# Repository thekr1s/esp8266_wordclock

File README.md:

# Get started on ubuntu 18.04 upto 20.04 (64 bits)
```
git clone https://github.com/thekr1s/esp8266_wordclock.git
cd esp8266_wordclock/esp-open-rtos
# NOTE Bearssl is outdated, and doesn't support CAfile, therefor disable check
git config --global http.sslverify false
git submodule update --init --recursive
cd ..
tar -xvf esp-open-sdk.tgz 
sudo apt-get install make gcc g++
sudo pip install esptool
. env.sh
cd wordclock
make
```

# Program ESP
## Windows
- Install ESP8266Flasher : https://github.com/nodemcu/nodemcu-flasher
- Install the driver for the USB2Sereial http://www.wch.cn/download/CH341SER_ZIP.html

Start the ESP8266Flasher.exe en vul het onderstaande in:

- esp8266_wordclock\esp-open-rtos\bootloader\firmware_prebuilt\rboot.bin            @ 0x00000
- esp8266_wordclock\esp-open-rtos\bootloader\firmware_prebuilt\blank_config.bin     @ 0x01000
- esp8266_wordclock\wordclock\firmware\ws2812_buffer.bin                            @ 0x02000

## Linux
After building the firmware with 'make' as discribed above, type the folliwing command:
```
make do_flash
```

# Setup Wordclock
- hierbenik: the request is build by: sprintf(buf, "GET %s HTTP/1.1\r\nHost: %s\r\nConnection:keep-alive\r\nAccept: */*\r\n\r\n", request, url);
- hierbenik request: "/get_with_age.php

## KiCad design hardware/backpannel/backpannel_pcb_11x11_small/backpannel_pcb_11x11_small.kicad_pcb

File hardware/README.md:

# Parts
## Electronics:
- NodeMcu Lolin V3 ESP32 [Link](https://www.ebay.com/itm/NodeMCU-V3-ESP8266-ESP-12-E-Lua-CH340-WiFI-WLan-IoT-Lolin-Mini-N3A2-V9T3/312753940110)
- Led strip: WS2812B [Link](https://www.ebay.com/itm/1-5m-WS2812B-RGB-Led-Strip-Light-30-60-144Leds-m-Individual-Addressable-IC-DC5V/401755047203?var=671534865138)
- LDR: 5MM GL5537 [Link](https://www.ebay.com/itm/20pcs-Photoresistor-5MM-GL5537-LDR-Photo-Resistors-Light-Dependent-Resistor/381374819080?epid=1381908731&hash=item58cbb5eb08:g:INIAAOxyYSdTAJq4)
- 100kOhm Resistor [link](https://www.ebay.com/itm/100PCS-1-4W-0-25W-Metal-Film-Resistor-1-Full-Range-of-Values-0-to-10M/252838503547?hash=item3ade59647b:m:m9AAPzkedx9P_upvXOpgF9Q) 
- flat cable
- Power wire
- micro USB
- USB A
## Shop / Bouwmarkt:
- For frames clock:
    - Ikea RIBBA frame 23cm [link](https://www.ikea.com/nl/nl/p/ribba-fotolijst-zwart-40378401/)
    - Ikea RIBBA frame 50cm [link](https://www.ikea.com/nl/nl/p/ribba-fotolijst-zwart-00378436/)
- Multiplex timmerplaat gegrond 3 mm 122x61
- MDF 122x61cm 12/15mm
- Hoekprofiel aluminium 12x12/15x15 mm 2 meter
- Bison 2-componentenlijm kombi metaal 24 ml
- Plaatschroef 3x13 mm cilinderkop
## Special:
- letterplate
    - laser cutting: €50.0/€150.0
- led-divider cnc: (time)

# Electronic Wiring
- ESP(Rx) -> Led Strip (Data)
- ESP(GND) -> Led Strip (GND)
- ESP(VU) -> Led Strip (5v)
- LDR(1) -> ESP(GND)
- LDR(2) -> ESP(A0)
- ESP(A0) -> RESISTOR(100kOhm) -> ESP(3v)

- 

# Build Types
The wordclock can be created in 2 sizes because of the used led strip. Its 60 LED's per meter or 30 LED's per meter.
## Normal (Desk size)
- 60 Leds per meter
    - 11x11 letters => 121 LED's => (2.01m) => 3 meter ledstrip
- 12mm MDF plate 23*23 cm
- Hardboard 23*23 cm
### Frame (ikea RIBBA) 

### Frameless

## Big clock (wall size)
The Big clock can be created with 11x11 letters or 13x13 letters
- 30 Leds per meter
    - 11x11 letters => 121 LED's => (4.04m) => 5 meter ledstrip
    - 13x13 letters => 169 LED's => (5.7m) => 6 meter ledstrip
- MDF plate 50*50 cm
- Hardboard 50*50 cm

### Frame 11x11 letters

### Frame 13x13 letters

### Frameless 13x13 letters

# Assemble
The assembly can be divided into the following parts:
- led-panel
- light-divider
- letterplate
- Electronics
## light-divider
### CNC light-divider

### light-divider by hand
For the famed Clock the MDF plate need's to be 23x23 or 50x50 cm. For the frameless the MDF plate can be LxB 21x20 or 45,5x47 but start with 23x23 or 50x50.
The Normal clock can be made with 9mm or 12mm MDF plate.
The big clock can be made with 12mm or 15mm MDF plate.
- Determine the center of the plate by drawing 2 lines
- From the center draw a grid of lines
    - For the 60 led's per meter -> distance between lines is 1.6666 cm
    - For the 30 led's per meter -> distance between lines is 3.3333 cm
- 
- Drill a hole through each line crossing
    - Use a speed drill or a countersink bit
    - For the normal clock the hole is 12mm
    - For the big clock the hole is 30mm
- For the frameless clock the bottom, right and left side can be shorted so the letterplate will floating from the wall ~15mm(aluminium strip width) + 2mm spare
    - The top side is used to hang the clock
- The result should look like the cnc light-divider

## led-panel
- Place the led-panel under the light-divider.
- Trace the first, middle and last holes from the light-divider on the led panel
- Trace the outer line from the light-divider
    - in case of the frameless the top can be shorten 2 cm
- Cut peace’s from the ledstrip, (cut on the line that is drawn on the 3 copper paths)
    - For the 11x11 clock the ledstrip should be 11 leds long 
    - For the 13x13 clock the ledstrip should be 13 leds long 
- Place the led-strips with the led centred on the traces on the hardboard by following the this pattern:
    - Start upper left with Din and place it to the upper Right side end with Dout
    - The second row start with Dout on the left side and ends with Din
    - continue this zigzag pattern until all rows are done
- Use a Flat cable to connect the ledstrips from Dout to Din.
    - Cut flat cable, strip and tin both ends, cut the both ends so they are separated from each other
    - pre-solder both ends of the ledstrip
    - Start upper right with Dout solder all 3 pins(GND, Dout, 5V) Fold the flat cable 90 degrees down, fold it 90 degrees towards Din Solder again
- drill a hole next to the first led, and next to the last led
- Connect power supply from the first led to the last led with the red/black wire
- Connect the powers supply and the Din with the ESP (see Electronic Wiring)
- 
- You should be able to test the LED panel by connection the ESP to its power supply

## Connect the led-panel with the light-divider
- Place the light-divider on the led-panel and make sure all leds are centred
- Drill (1.5mm) hole through both panels. These hols can later be used to connect both panels
- Flip it and screw both panels to each other.
- Frameless ESP placement
    - Big clock place the ESP in the upper right corner (hot glue)
    - Normal clock the ESP will be screwed to the back
- 

## Diffuser (to be improved)
- place the paper over the light-divider and cut it on size
- make sure its stays in place with tape

## Letterplate
### frame
- Connect the LDR and the resistor (see Electronic Wiring)
- fix the ESP with a screw to the back of the led-panel
- Place the letterplate and the light divider in the frame
- place some foam in the back so all is pushed forwarded
- Close the frame
### frameless
- Center the light-divider on the letterplate and drill the LDR hole
- Draw the outer line from the light-divider on theletterplates back
- Cut the aluminium strip so it fits nicely around the light-divider (left, right and bottom)
- Make both the letterplate and the aluminium strip rough with sanding paper
- drill 3 holes in all aluminium strips (used for connecting the letterplate to the light-divider)
- glue the aluminium strip on the letterplate (use glue clamps) wait 24 hours
- screw the letterplate to the light-divider
- 

# Hardware Drawings
## letterplate
- I Have created a FreeCAD pyhton macro for generating a Letterplate, ..\hardware\lettering_plates\FreeCAD_drawings\freecad_macro
- The letterplate is parametric so can be used for 11*11 of 13*13
- After the generation is done, export the part as .STEP (the DXF generator from freecad is not smooth)
- FreeCAD export DXF WORKS (0.18.4):
    - Edit -> Preference -> Inport-Export -> DXF
    - Max Spline Segment to 0,1 or 0,01 mm (NOTE use , instead of .)
    - Select all elements
    - File -> Export -> Autodesk DXF 2d
- Import the .STEP file into Fusion for creating the DXF file of gcode
- G-code
    - Create A body by setting the Hight
    - Switch to manufacture
    - start creating the Gcode
- DXF:
    - Create a sketch on the Top view
    - Menu -> Create -> Project / include -> include 3D Geometry
    - Select the Body from the letterplate
    - Save Sketch -> right klik the Sketch and save as DXF
## ledschotten
- The LDR for the 11*11 clock is 214.444 mm from the bottom (This information is printed by FreeCAD)
- The LDR for the 13*13 clock is 477.778 mm from the bottom
- The LEDschotten is completely drawn in Fusion360, and is partly parametric.

# Tips & tricks:
- The MDF plate can also be replaced by "Foamed pvc"

# Note:
The NodeMcu Lolin V3 is needed because the Lolin has a 3v reference voltage for its adc that is used for the LDR all other NodeMC have 1v reference voltage

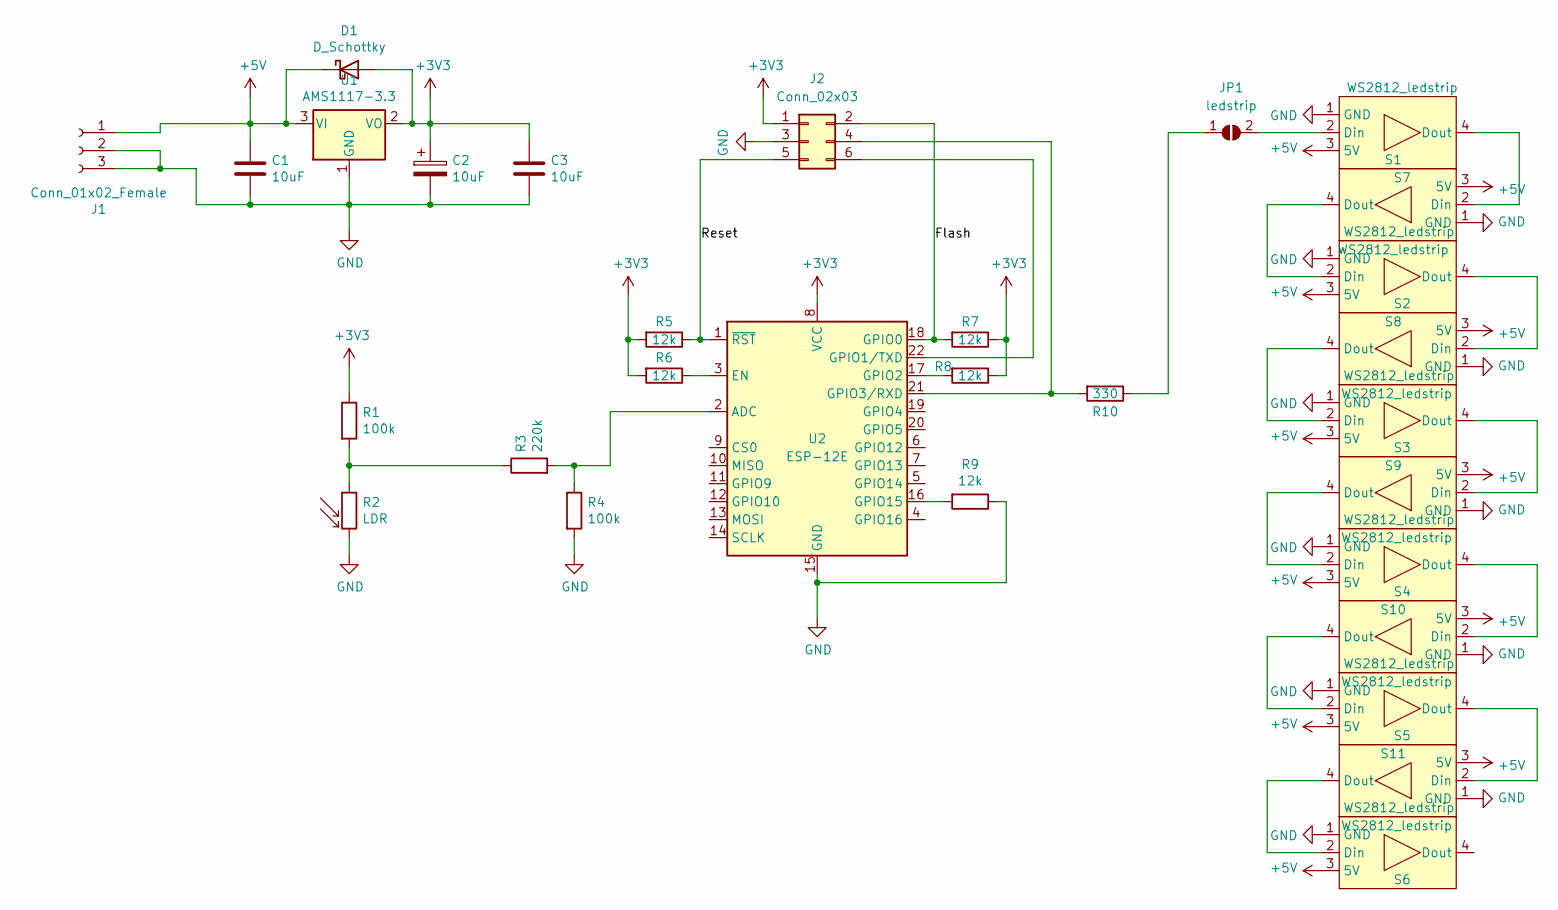
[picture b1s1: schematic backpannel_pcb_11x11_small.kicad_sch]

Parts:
C1, C3: 10uF; C_0805_2012Metric_Pad1.18x1.45mm_HandSolder
C2: 10uF; CP_Elec_6.3x5.4
D1: D_Schottky; D_0805_2012Metric_Pad1.15x1.40mm_HandSolder
J1: Conn_01x02_Female; BarrelJack_CLIFF_FC681465S_SMT_Horizontal
J2: Conn_02x03; PinHeader_2x03_P2.54mm_Vertical
JP1: ledstrip; SolderJumper-2_P1.3mm_Open_RoundedPad1.0x1.5mm
R1, R4: 100k; R_0805_2012Metric_Pad1.20x1.40mm_HandSolder
R2: LDR; R_LDR_5.1x4.3mm_P3.4mm_Vertical
R3: 220k; R_0805_2012Metric_Pad1.20x1.40mm_HandSolder
R5, R6, R7, R8, R9: 12k; R_0805_2012Metric_Pad1.20x1.40mm_HandSolder
R10: 330; R_0805_2012Metric_Pad1.20x1.40mm_HandSolder
S1, S2, S3, S4, S5, S6, S7, S8, S9, S10, S11: WS2812_ledstrip; WS2812_ledstrip_60leds_meter
U1: AMS1117-3.3; SOT-223-3_TabPin2
U2: ESP-12E

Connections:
+3V3: C2.1, C3.1, D1.2 (A), J2.1, R1.1, R5.2, R6.2, R7.1, R8.1, U1.2 (VO), U2.8 (VCC)
+5V: C1.1, D1.1 (K), J1.1, S1.3 (5V), S2.3 (5V), S3.3 (5V), S4.3 (5V), S5.3 (5V), S6.3 (5V), S7.3 (5V), S8.3 (5V), S9.3 (5V), S10.3 (5V), S11.3 (5V), U1.3 (VI)
/Flash: J2.2, R7.2, U2.18 (GPIO0)
/Reset: J2.5, R5.1, U2.1 (~RST)
GND: C1.2, C2.2, C3.2, J1.2, J1.3, J2.3, R2.2, R4.2, R9.1, S1.1 (GND), S2.1 (GND), S3.1 (GND), S4.1 (GND), S5.1 (GND), S6.1 (GND), S7.1 (GND), S8.1 (GND), S9.1 (GND), S10.1 (GND), S11.1 (GND), U1.1 (GND), U2.15 (GND)
unnamed: J2.4, R10.2, U2.21 (GPIO3/RXD)
unnamed: J2.6, U2.22 (GPIO1/TXD)
unnamed: JP1.1 (A), R10.1
unnamed: JP1.2 (B), S1.2 (Din)
unnamed: R1.2, R2.1, R3.1
unnamed: R3.2, R4.1, U2.2 (ADC)
unnamed: R6.1, U2.3 (EN)
unnamed: R8.2, U2.17 (GPIO2)
unnamed: R9.2, U2.16 (GPIO15)
unnamed: S1.4 (Dout), S7.2 (Din)
unnamed: S2.2 (Din), S7.4 (Dout)
unnamed: S2.4 (Dout), S8.2 (Din)
unnamed: S3.2 (Din), S8.4 (Dout)
unnamed: S3.4 (Dout), S9.2 (Din)
unnamed: S4.2 (Din), S9.4 (Dout)
unnamed: S4.4 (Dout), S10.2 (Din)
unnamed: S5.2 (Din), S10.4 (Dout)
unnamed: S5.4 (Dout), S11.2 (Din)
unnamed: S6.2 (Din), S11.4 (Dout)

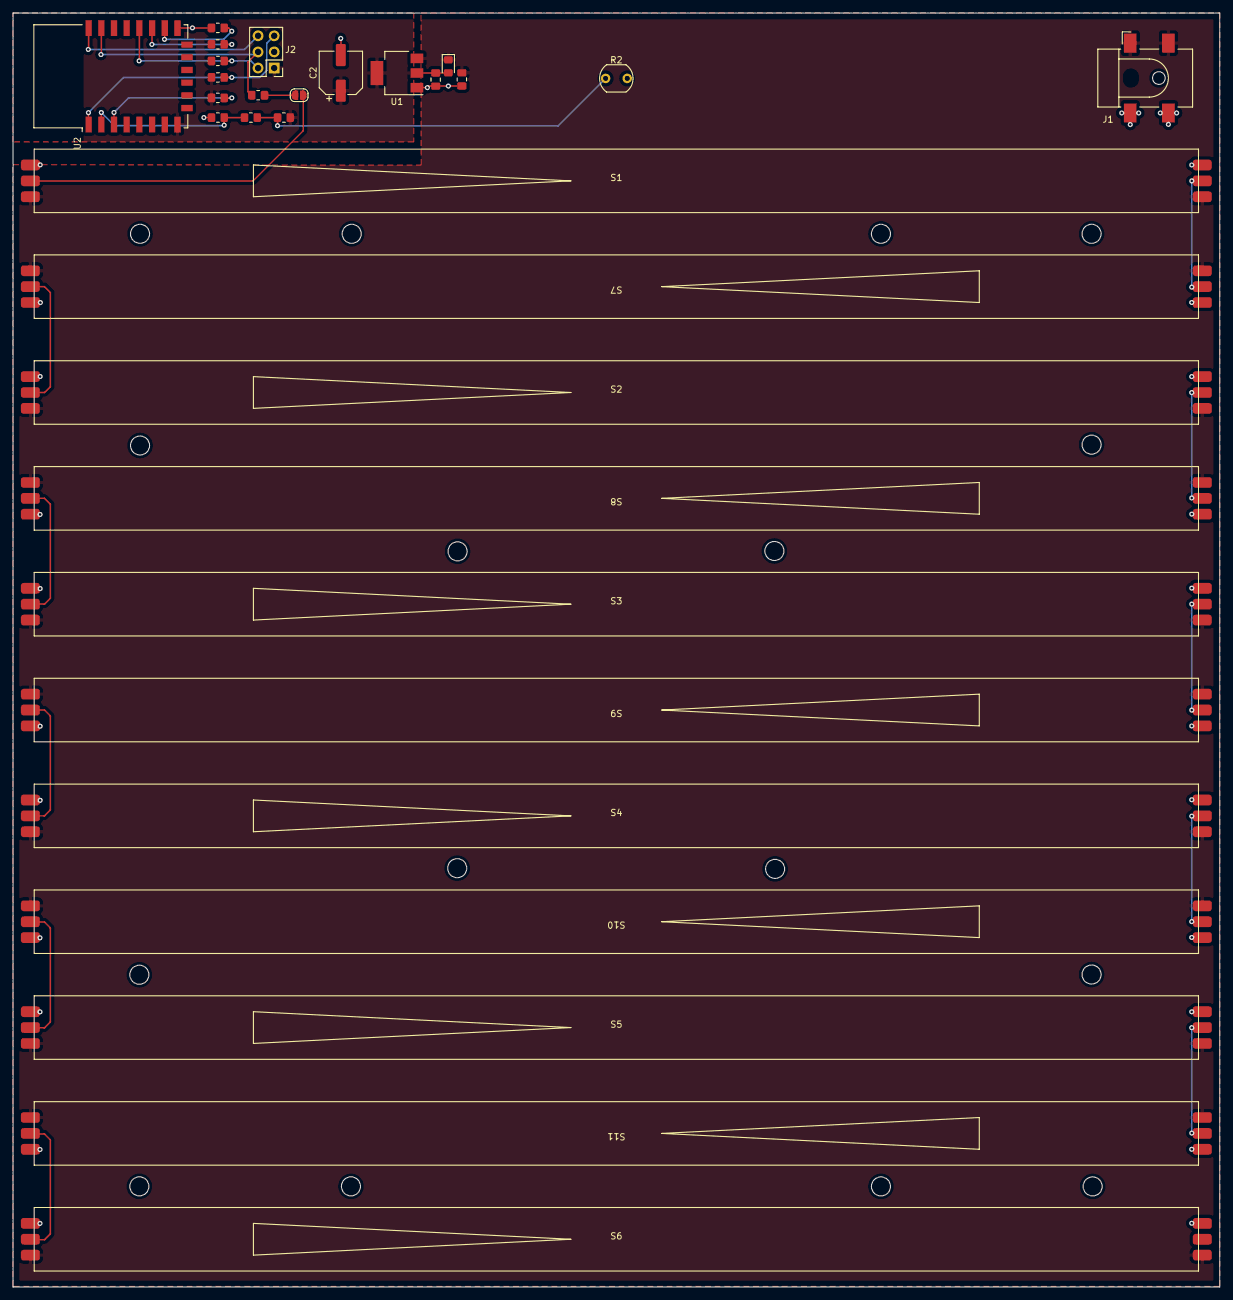
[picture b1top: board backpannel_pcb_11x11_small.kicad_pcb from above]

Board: 2 copper layers, 190.0 x 200.6 mm, 30 parts (0 on the bottom side), 24 nets.

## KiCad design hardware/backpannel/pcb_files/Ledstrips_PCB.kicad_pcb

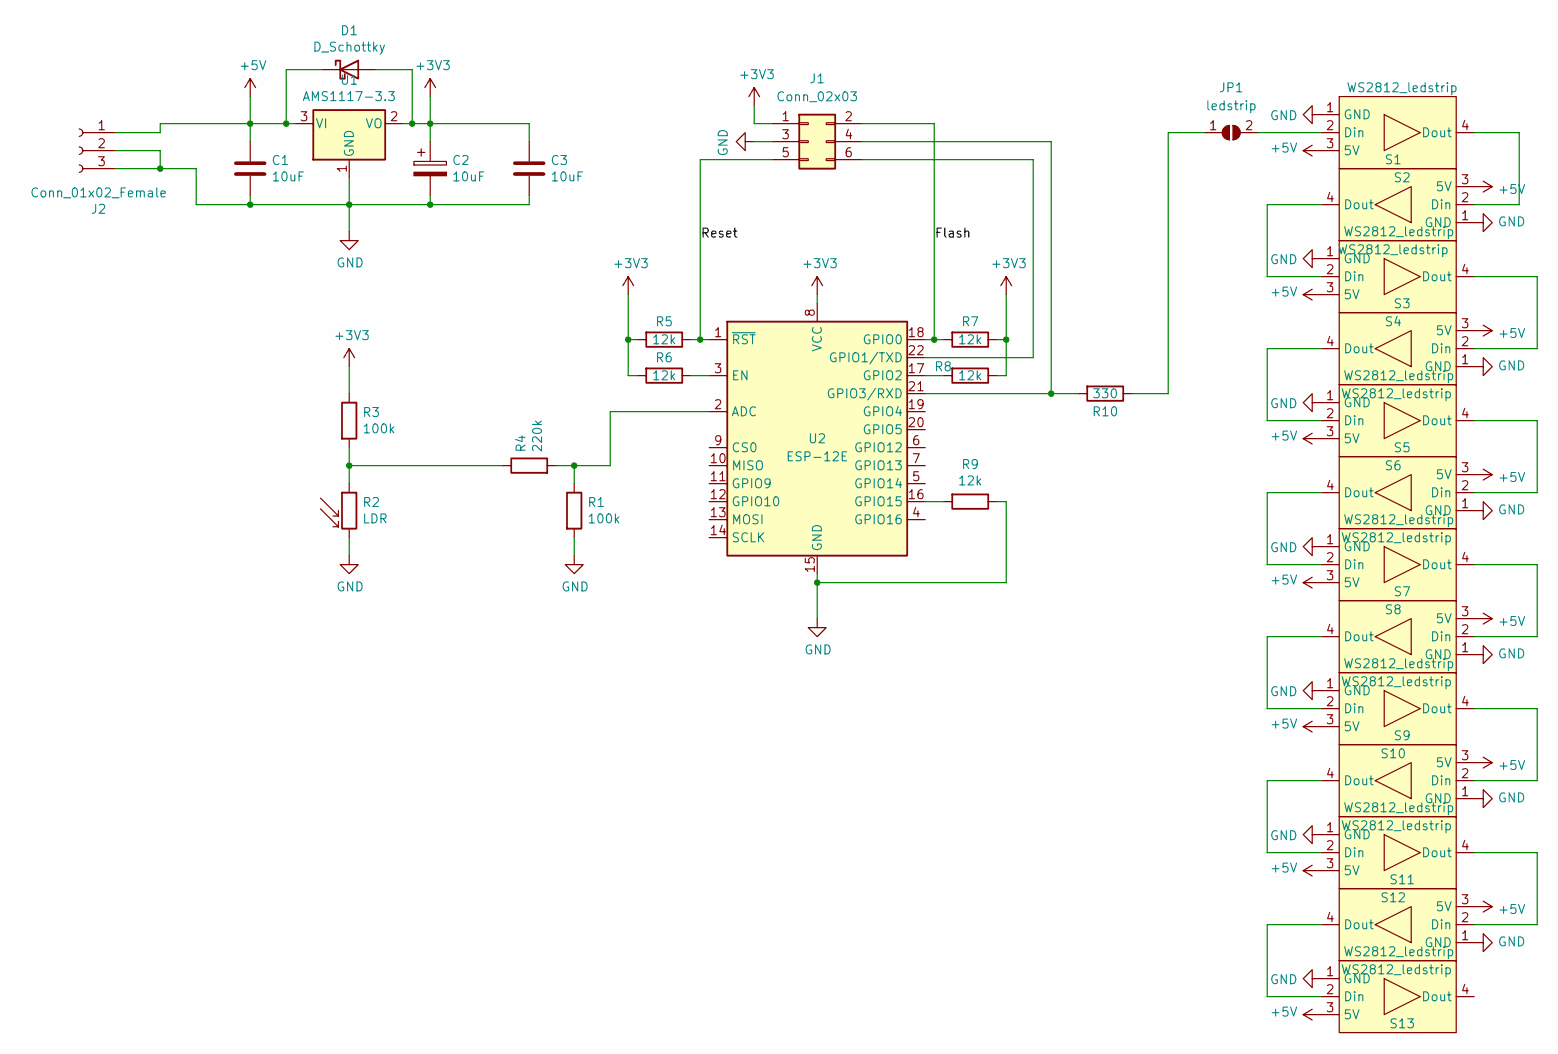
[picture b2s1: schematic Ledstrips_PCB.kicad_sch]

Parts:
C1, C3: 10uF; C_0805_2012Metric_Pad1.18x1.45mm_HandSolder
C2: 10uF; CP_Elec_6.3x5.4
D1: D_Schottky; D_0805_2012Metric_Pad1.15x1.40mm_HandSolder
J1: Conn_02x03; PinHeader_2x03_P2.54mm_Vertical
J2: Conn_01x02_Female; BarrelJack_CLIFF_FC681465S_SMT_Horizontal
JP1: ledstrip; SolderJumper-2_P1.3mm_Open_RoundedPad1.0x1.5mm
R1, R3: 100k; R_0805_2012Metric_Pad1.20x1.40mm_HandSolder
R2: LDR; R_LDR_5.1x4.3mm_P3.4mm_Vertical
R4: 220k; R_0805_2012Metric_Pad1.20x1.40mm_HandSolder
R5, R6, R7, R8, R9: 12k; R_0805_2012Metric_Pad1.20x1.40mm_HandSolder
R10: 330; R_0805_2012Metric_Pad1.20x1.40mm_HandSolder
S1, S2, S3, S4, S5, S6, S7, S8, S9, S10, S11, S12, S13: WS2812_ledstrip; WS2812_ledstrip_30leds_meter
U1: AMS1117-3.3; SOT-223-3_TabPin2
U2: ESP-12E

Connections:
+3V3: C2.1, C3.1, D1.2 (A), J1.1, R3.1, R5.2, R6.2, R7.1, R8.1, U1.2 (VO), U2.8 (VCC)
+5V: C1.1, D1.1 (K), J2.1, S1.3 (5V), S2.3 (5V), S3.3 (5V), S4.3 (5V), S5.3 (5V), S6.3 (5V), S7.3 (5V), S8.3 (5V), S9.3 (5V), S10.3 (5V), S11.3 (5V), S12.3 (5V), S13.3 (5V), U1.3 (VI)
/Flash: J1.2, R7.2, U2.18 (GPIO0)
/Reset: J1.5, R5.1, U2.1 (~RST)
GND: C1.2, C2.2, C3.2, J1.3, J2.2, J2.3, R1.2, R2.2, R9.1, S1.1 (GND), S2.1 (GND), S3.1 (GND), S4.1 (GND), S5.1 (GND), S6.1 (GND), S7.1 (GND), S8.1 (GND), S9.1 (GND), S10.1 (GND), S11.1 (GND), S12.1 (GND), S13.1 (GND), U1.1 (GND), U2.15 (GND)
unnamed: J1.4, R10.2, U2.21 (GPIO3/RXD)
unnamed: J1.6, U2.22 (GPIO1/TXD)
unnamed: JP1.1 (A), R10.1
unnamed: JP1.2 (B), S1.2 (Din)
unnamed: R1.1, R4.2, U2.2 (ADC)
unnamed: R2.1, R3.2, R4.1
unnamed: R6.1, U2.3 (EN)
unnamed: R8.2, U2.17 (GPIO2)
unnamed: R9.2, U2.16 (GPIO15)
unnamed: S1.4 (Dout), S2.2 (Din)
unnamed: S2.4 (Dout), S3.2 (Din)
unnamed: S3.4 (Dout), S4.2 (Din)
unnamed: S4.4 (Dout), S5.2 (Din)
unnamed: S5.4 (Dout), S6.2 (Din)
unnamed: S6.4 (Dout), S7.2 (Din)
unnamed: S7.4 (Dout), S8.2 (Din)
unnamed: S8.4 (Dout), S9.2 (Din)
unnamed: S9.4 (Dout), S10.2 (Din)
unnamed: S10.4 (Dout), S11.2 (Din)
unnamed: S11.4 (Dout), S12.2 (Din)
unnamed: S12.4 (Dout), S13.2 (Din)

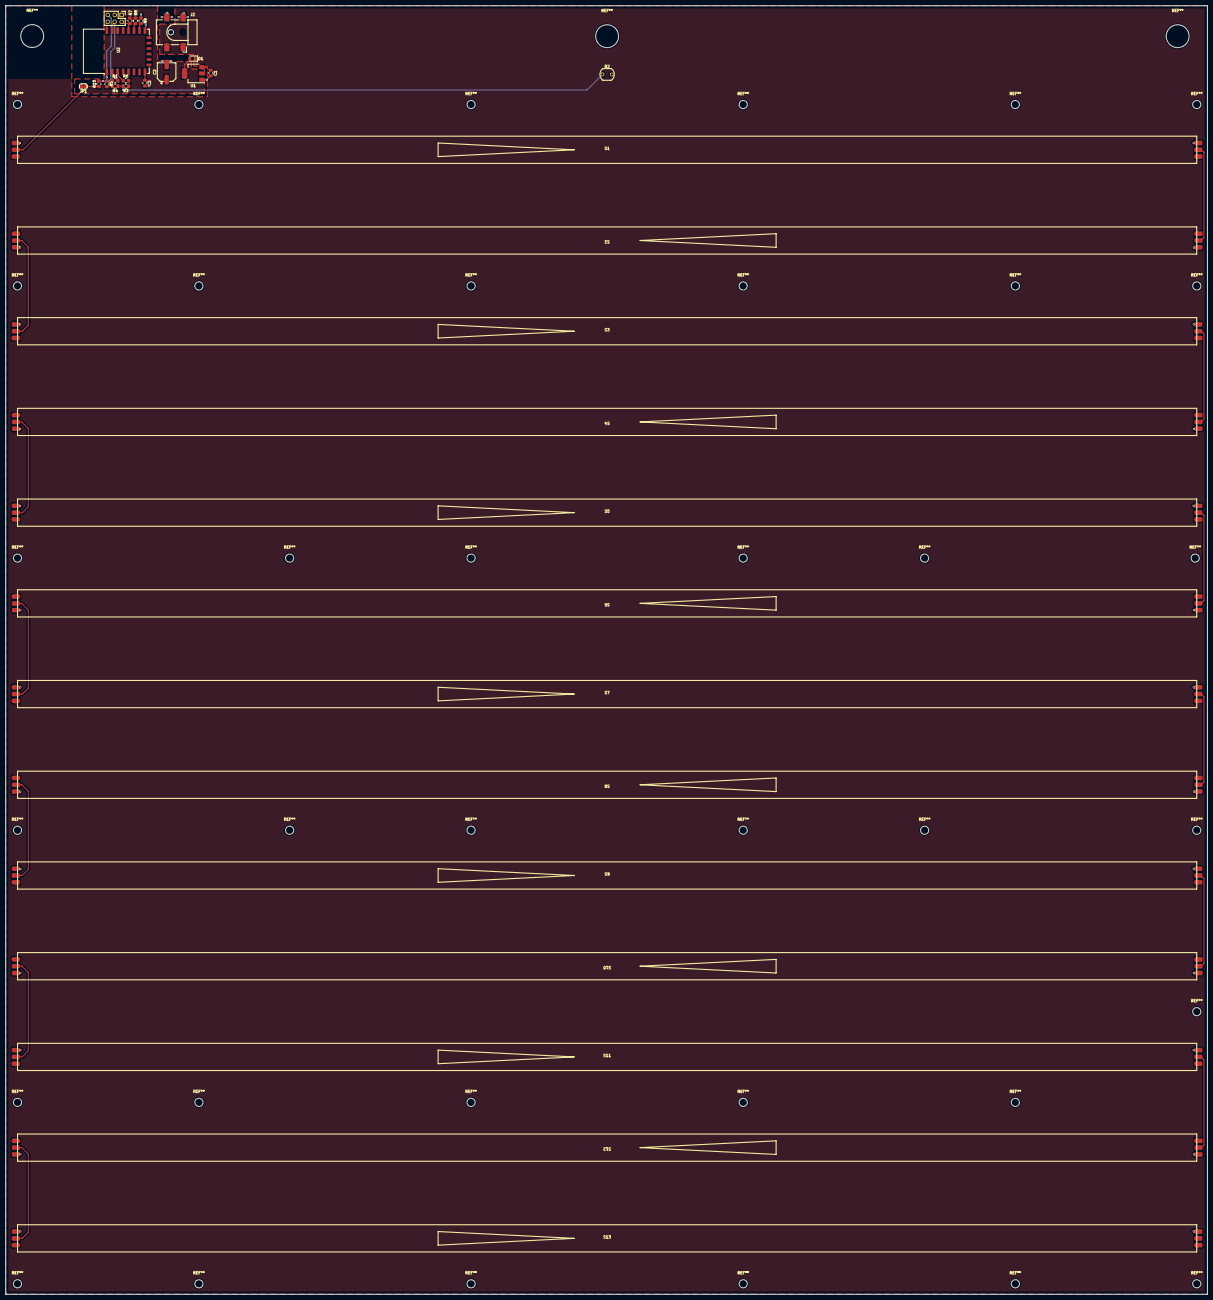
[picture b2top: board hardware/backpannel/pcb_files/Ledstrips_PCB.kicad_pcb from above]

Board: 2 copper layers, 441.6 x 473.5 mm, 32 parts (0 on the bottom side), 26 nets.

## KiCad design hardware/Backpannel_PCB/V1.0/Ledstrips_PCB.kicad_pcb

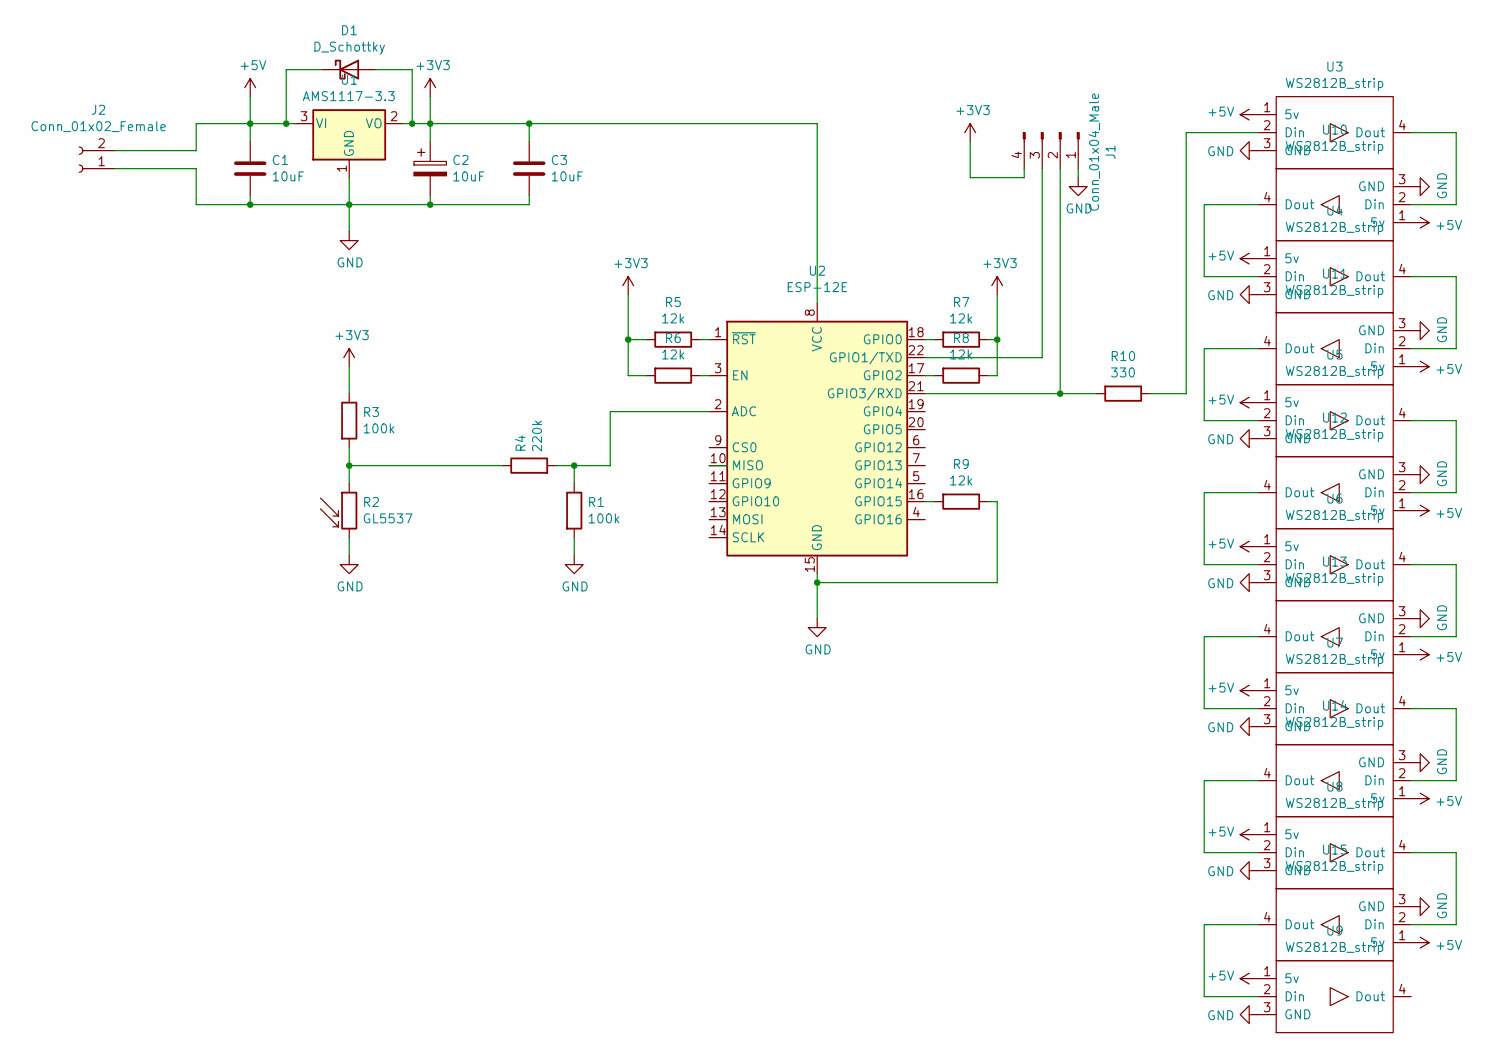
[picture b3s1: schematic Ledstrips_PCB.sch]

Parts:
C1, C3: 10uF; C_0603_1608Metric_Pad1.08x0.95mm_HandSolder
C2: 10uF; CP_Elec_3x5.4
D1: D_Schottky; D_0603_1608Metric_Pad1.05x0.95mm_HandSolder
J1: Conn_01x04_Male; PinHeader_1x04_P2.54mm_Vertical
J2: Conn_01x02_Female; BarrelJack_CLIFF_FC681465S_SMT_Horizontal
R1, R3: 100k; R_0603_1608Metric_Pad0.98x0.95mm_HandSolder
R2: GL5537; R_LDR_5.0x4.1mm_P3mm_Vertical
R4: 220k; R_0603_1608Metric_Pad0.98x0.95mm_HandSolder
R5, R6, R7, R8, R9: 12k; R_0603_1608Metric_Pad0.98x0.95mm_HandSolder
R10: 330; R_0603_1608Metric_Pad0.98x0.95mm_HandSolder
U1: AMS1117-3.3; SOT-223-3_TabPin2
U2: ESP-12E
U3, U4, U5, U6, U7, U8, U9, U10, U11, U12, U13, U14, U15: WS2812B_strip; ws2812_ledstrip

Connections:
+3V3: C2.1, C3.1, D1.2 (A), J1.4, R3.1, R5.2, R6.2, R7.1, R8.1, U1.2 (VO), U2.8 (VCC)
+5V: C1.1, D1.1 (K), J2.2, U1.3 (VI), U3.1 (5v), U4.1 (5v), U5.1 (5v), U6.1 (5v), U7.1 (5v), U8.1 (5v), U9.1 (5v), U10.1 (5v), U11.1 (5v), U12.1 (5v), U13.1 (5v), U14.1 (5v), U15.1 (5v)
GND: C1.2, C2.2, C3.2, J1.1, J2.1, R1.2, R2.2, R9.1, U1.1 (GND), U2.15 (GND), U3.3 (GND), U4.3 (GND), U5.3 (GND), U6.3 (GND), U7.3 (GND), U8.3 (GND), U9.3 (GND), U10.3 (GND), U11.3 (GND), U12.3 (GND), U13.3 (GND), U14.3 (GND), U15.3 (GND)
unnamed: J1.2, R10.2, U2.21 (GPIO3/RXD)
unnamed: J1.3, U2.22 (GPIO1/TXD)
unnamed: R1.1, R4.2, U2.2 (ADC)
unnamed: R2.1, R3.2, R4.1
unnamed: R5.1, U2.1 (~RST)
unnamed: R6.1, U2.3 (EN)
unnamed: R7.2, U2.18 (GPIO0)
unnamed: R8.2, U2.17 (GPIO2)
unnamed: R9.2, U2.16 (GPIO15)
unnamed: R10.1, U3.2 (Din)
unnamed: U3.4 (Dout), U10.2 (Din)
unnamed: U4.2 (Din), U10.4 (Dout)
unnamed: U4.4 (Dout), U11.2 (Din)
unnamed: U5.2 (Din), U11.4 (Dout)
unnamed: U5.4 (Dout), U12.2 (Din)
unnamed: U6.2 (Din), U12.4 (Dout)
unnamed: U6.4 (Dout), U13.2 (Din)
unnamed: U7.2 (Din), U13.4 (Dout)
unnamed: U7.4 (Dout), U14.2 (Din)
unnamed: U8.2 (Din), U14.4 (Dout)
unnamed: U8.4 (Dout), U15.2 (Din)
unnamed: U9.2 (Din), U15.4 (Dout)

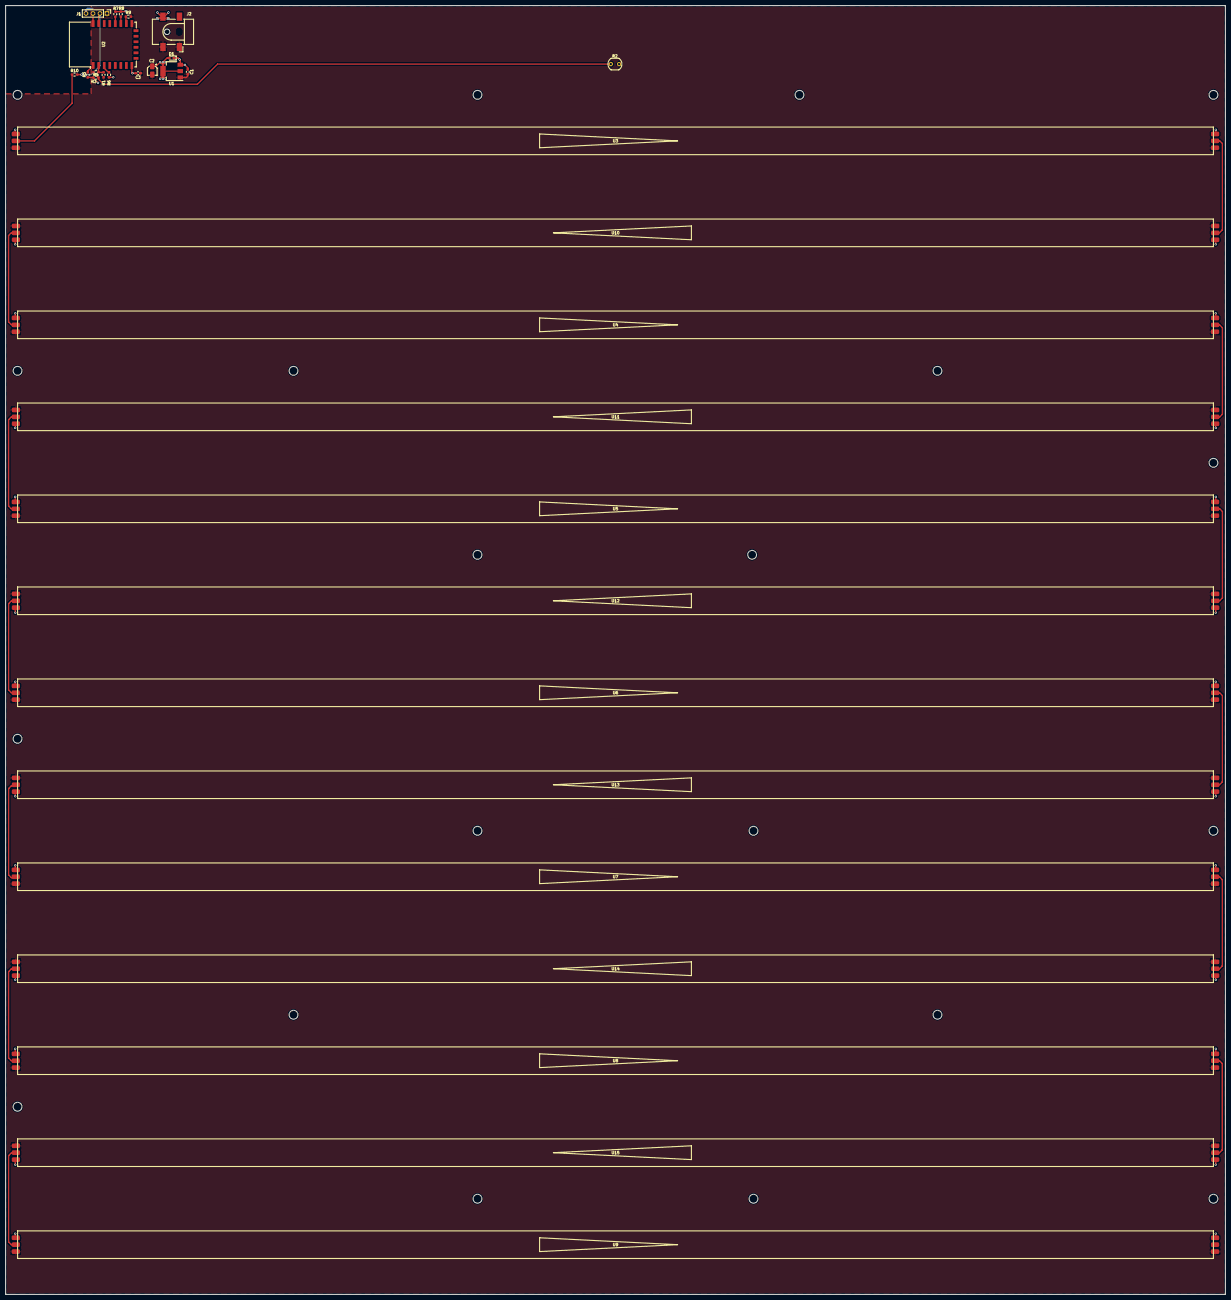
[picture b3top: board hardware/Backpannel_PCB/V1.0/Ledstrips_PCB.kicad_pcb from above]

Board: 2 copper layers, 442.0 x 467.0 mm, 31 parts (0 on the bottom side), 25 nets.

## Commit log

2018-02-27 Initial comit from svn archive
2018-02-28 add esp-open-rtos patch
2018-02-28 ad toolchain in tar update readme
2018-02-28 remove svnversion from makefile
2018-03-02 Add wipe effect
2018-03-02 add the color rainbow
2018-03-02 fixed 13*13 word faults
2018-03-03 Hierbenik implemented for rutger
2018-03-03 small change to the readme
2018-03-03 added a git ignore file for build results
2018-03-11 increase wipe refresh speed
2018-03-15 renamed ALSFILER_RANDOM
2018-04-05 Add hostname to dhcp request
2018-04-05 undo previous commit
2018-10-22 add git version number in build
2018-10-23 display message when no wifi connection
2019-08-17 includes all my spilt files into this git repo so i/we don't loose any information, it still need some cleaning
2019-08-18 Included freecad tekening
2019-08-18 saved a wordclock without squares
2019-08-20 Freecad draw schotten
2019-08-23 impl for big scots
2019-09-05 split the code into modules, and made a 11X11 clock
2019-09-09 created own font, and some fixes for 11*11 clock
2019-09-09 moved freecad folder
2019-09-25 removed wrong DXF files and fix import
2019-09-25 moved files
2019-11-18 Fix good rainbow color ;-)
2019-11-18 fix rainbow
2019-11-20 update hardware
2019-11-25 uploaded letterplate 11x11 and made env.sh system independed
2019-11-26 letterplaten en gatenboards
2019-11-26 verplaats gatenboard
2019-11-26 add came controller and breakout first version
2019-12-30 updated hardware drawings
2019-12-30 Made Personalized setting configurable through hwcfg
2019-12-30 fix empty settings, and checkbox default on
2019-12-30 also do not clear port number and "wacht even" under perfect imperfections
2019-12-30 Show the current settings in the webpage
2020-01-01 fix checkbox unselected
2020-01-04 fix code revieuw RWA
2020-01-05 default ota server and fix zerotermination
2020-01-05 Removed esp-open-rtos
2020-01-05 Added new version of esp-open-rtos as submodule
2020-01-05 made the new esp_open_rtos build (still a bug in the ledstrip driver)
2020-01-06 change from 3 to 4 bits per pixel
2020-01-07 fixed private_ssid_config
2020-01-22 tetris wip. Not done yet
2020-01-24 apply rainbow filter before hierbenik position to make it more visible
2020-01-24 configurable home location
2020-01-25 fix bool build problem
2020-01-25 remove commented code
2020-01-27 Fix stack crash when in AP mode
2020-01-27 get rid of rtos patches
2020-01-27 fix compiler warnings
2020-01-28 hopefully fix klok op hol
2020-01-29 web pages update
2020-02-02 WIFI AP config via dropdown select
2020-02-02 increase flash upload speed
2020-02-02 reduce debug print outout
2020-02-12 process review
2020-02-12 freecad macro changes
2020-02-15 Upload last generated version of letterplaats G-code
2020-02-22 Revert "Update freecad macro"
2020-02-22 Updated the 11x11 and 13x13 letterplate for RHU, liberation is smoother now, removed unneded points in font to create nice arc
2020-03-06 add kiremko logo
2020-03-11 fix breakout
2020-04-07 add the new drawings RHU
2020-04-18 Changed esp-open-rtos url to own fork
2020-04-18 revert sntp_client
2020-04-20 Initial impl for captive DNS
2020-04-20 Fixed assert in OS, and lower the wordclock main so AP mode has more time
2020-04-20 revert prio change will fix in a other branch
2020-04-20 Cleanup hardware drawing RHU
2020-04-20 Initial captive DNS
2020-04-20 Fix hardware readme
2020-04-21 Update Makefile
    Remove high speed flash programming as it is suspected to destroy the flash
2020-04-22 quick fix for settings
2020-04-23 Added fixed hardware drawing
2020-04-23 Settings are stored throug the sysparam key=value
2020-04-23 update esp-open-rtos for new wifi-cfg
2020-04-23 fixed some logging and dontt run the wordklok main when we have no time
2020-04-23 keep default settings in flash, not ram
2020-04-24 added some sleeps in woordklokmain
2020-04-25 reorderd init and fixed some concurrensi issues
2020-04-29 kill the wordclock task when there is no wifi
2020-04-29 changed prio
2020-04-30 fault handling in starting http server
2020-04-30 remove URLs from readme
2020-05-01 Fix issue when sntp is out of sync
2020-05-01 Made the HTTP socket reusable
2020-05-02 add params to esptools in makefile
2020-05-03 add old firmware binary
2020-05-09 rename to woordklok.bin
2020-05-09 Update build.yml
    A
2020-05-10 Initial merge
2020-05-10 decreased sntp stack
2020-05-11 Processed review comment RWA
2020-05-11 Initial impl for sysparam fix
2020-05-12 Final version of sysparam test
2020-05-12 Moved the connection check in a task so the esp framework finishs its init before starting in ap mode
2020-05-14 Increased woordklok display task prio
2020-05-14 revert dns server code
2020-05-15 Added the release binary
2020-07-10 None functional only hardware en readme changes
2020-07-10 Initial version need to be tested (but nog ESP at work)
2020-07-10 fix logging
2020-07-11 fixed HTML layout
2020-07-11 changed setting magic
2020-07-13 Initial impl
2020-07-17 Correct Time on boot properly
2020-08-03 Captive DNS within our own website
2020-08-05 Update http_server.c
    Resolve merge conflict (FW type was missing)
2020-08-05 fix email address on web page
2020-08-06 Add break after, refresh page
2020-08-08 Initial version for color picker and better response for wifi ap scan
2020-08-11 improve wifi minitor task
2020-08-11 initial version http ota update
2020-08-15 Fixed ap scan task
2020-08-28 set http as default
2020-08-30 Revert "Merge pull request #44 from thekr1s/ubuntu_20.04"
    This reverts commit 86ca58a5fa7ca427b36f4038e63310cc08924adf, reversing
    changes made to b96e6bfef97ccbdc93eba87d549ee790450c63f4.
2020-09-01 strip CRC from firmware file
2020-09-01 do not erase wifi settings on factory reset
2020-09-06 Color picker with embedded IRO.js
2020-09-06 add letterplate_13_13
2020-09-06 only strip crc from binary when make do_flash
2020-09-06 some styling, and forced Saturation and Alpha for background color
2020-09-06 remove comment
2020-09-06 Rutgers Build default settings
2020-09-06 More robust color picker
2020-09-06 use esp-open-rtos from fork on thekr1s
2020-09-12 Revert make file to strip CRC default
2020-09-12 Make the rainbow effect working again
2020-09-12 Removed Background color offset
2020-09-12 Removed the color picker popup
2020-09-12 white space
2020-09-12 Fix color picker scaling for android Chrome
2020-09-12 Fix hangup in http server when client is not properly closing socket
2020-10-12 inital change, needs spelling check and reread it
2020-10-24 Spell checker
2020-10-24 Forget file...
2020-11-14 Move version info to system config tab
2020-11-14 fix in reboot clock
2020-11-14 update connect to wifi text
2020-11-14 sort AP list by strength
2020-11-14 shorten no wifi sentence
2020-11-14 set stationmode befere restart
2020-11-18 fix wifi cinfig in httpsvr
2020-11-19 add IJ to taurus font
2020-11-20 drawing 120x120 housing
2020-11-22 120 housing update
2020-12-30 manual update
2021-01-23 Reduce mem usage to preven alloc error at otaupdate
2021-01-24 improve backgroung handling
2021-01-24 put timesync error indication at top right
2021-02-27 bump esp-open-rtos
2021-02-28 fix button handling
2021-05-16 Set random color every hour
2021-05-16 move MAX macro
2021-05-16 spaces
2021-05-16 more spaces
2021-11-24 initial RGB to RGBW support
2021-12-01 fix enum numer
2021-12-18 added debug webpage for LDR and way to use rgbw ledstrip without the white led
2021-12-18 First version of PCB
2021-12-21 Added non accurate time for 13x13
2021-12-21 Remove unwaded make flag
2021-12-28 added new line
2022-02-02 Fixed fire animation for 13x13 clock
2022-02-02 renamed folder
2022-02-02 rename
2022-02-09 Initial change
2022-02-09 Add install instructions
2022-02-16 13x13 letterplate V2
2022-02-16 Added Qcad converted file
2022-02-23 PCB in between commit
2022-02-23 wifi soft AP accourding to sdk status
2022-03-09 Also updated to HTTP server (tftp is block by some modums)
2022-03-20 don't store the white value in the frame buffer
2022-03-22 Moved copy action to write function
2022-03-22 cleanup names in callback
2022-03-22 Added the new letterplate to the SW
2022-04-20 Fix 13x13 layout, and buffer size
2022-05-04 Added extra SNTP servers through sntp.h (see submodule), fixed core lock, refactord wificfg
2022-05-04 Removed the button task and event handler
2022-05-04 Splitted settings into two flash partitions, with separated magics
2022-05-07 Added reserved space in both setting so the magic is more stable
2022-05-08 All set opmode in 1 task, and cleanup statemachine
2022-05-11 Fixed reboot issues
2022-05-11 Cleaner stop of soft AP
2022-05-30 None functional, only pointed to the proper esp-open-rtos branch
2022-06-22 Updated PCB and ledschotten
2022-11-27 update PCB and ngc files for 13x13 clock
2022-11-28 Finisched PCB
2022-11-28 Added project for 11x11
2022-11-30 placement 11x11
2023-01-22 finished hardware for small and big clock
2023-01-22 Updated manual
2023-10-06 Added all kinds of nieuw hardware
2023-10-06 Added configuration for timezone and DST setting
2023-10-08 processed review RWA
2023-10-08 Fix regex time range
2023-10-08 Fix stupit way of printing and wrong substraction
2023-11-06 increase do_flash uart speed
2023-11-06 add user-agent to http-request
2023-11-06 fix hierbenik at startup
2023-11-06 more frequent hierbenik checks
2024-03-22 functional RDS
2024-03-25 start radio as last
2024-03-26 Remove buttons, delayed radio int and more cleanup
2024-04-09 Add radio rssi to debug page
2024-07-01 Initial commit for wled realtime UDP recv to display
2024-07-01 only NC files
2024-07-02 Fixed timeout and position
2024-07-03 Added the game snake and fixed some api
2024-07-03 add note for row inversion
2024-07-20 fix buffer overrun
2024-07-26 Initial brainfart
2024-10-23 Fix delayed http msg
2024-10-23 Fixed http delayed msg
2024-10-23 Fix for github build?
2024-10-23 changed pixelkast remote URL to HTTPS
2024-10-24 improvements
2024-10-24 chmod +x
2024-10-27 improved woordklok api and update pixelkast submodule
2024-10-27 Added sleep in case of invalid recv
2024-10-27 Added sleep in case realtime-udp failes
2025-01-11 Added a new version for the klock woords layout, requested by someone
2025-01-25 update manual
2025-01-25 remove kastgame module
2025-01-25 cleanup
2025-05-27 expose LED and LDR values in webpage
2025-05-27 fix style
2025-05-27 remove debug line and fix DNS and rutger build
2025-05-27 Added LUT generator + update values
2025-12-17 added rhu env
